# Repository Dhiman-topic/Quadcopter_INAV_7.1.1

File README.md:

# Quadcopter_INAV_7.1.1
 This project is about to make a home made quadcopter using aluminium frame and diy pcb

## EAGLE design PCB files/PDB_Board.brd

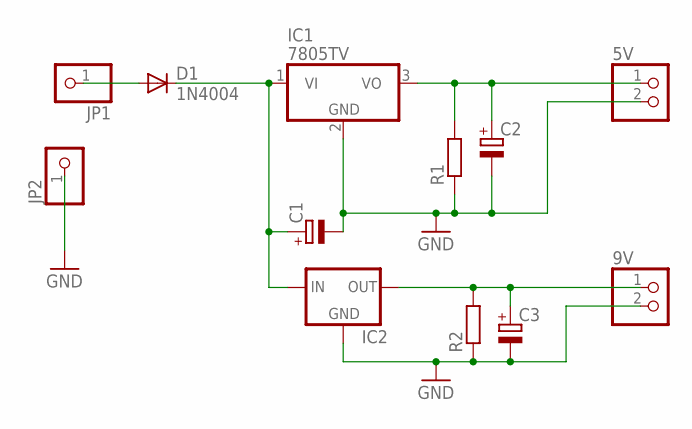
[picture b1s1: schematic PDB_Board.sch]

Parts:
5V, 9V: PINHD-1X2/OCT; 1X02/OCT
C1: CPOL-EUE3.5-8; E3,5-8
C2, C3: CPOL-EUE2.5-5; E2,5-5
D1: 1N4004; DO41-10
IC1: 7805TV; TO220V
IC2: 78XXS
JP1, JP2: PINHD-1X1; 1X01
R1, R2: R-EU_0207/10; 0207/10

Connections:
GND: 5V.2, 9V.2, C1.-, C2.-, C3.-, IC1.2 (GND), IC2.GND, JP2.1, R1.1, R2.1
unnamed: C1.+, D1.C, IC1.1 (VI), IC2.IN
unnamed: 9V.1, C3.+, IC2.OUT, R2.2
unnamed: 5V.1, C2.+, IC1.3 (VO), R1.2
unnamed: D1.A, JP1.1

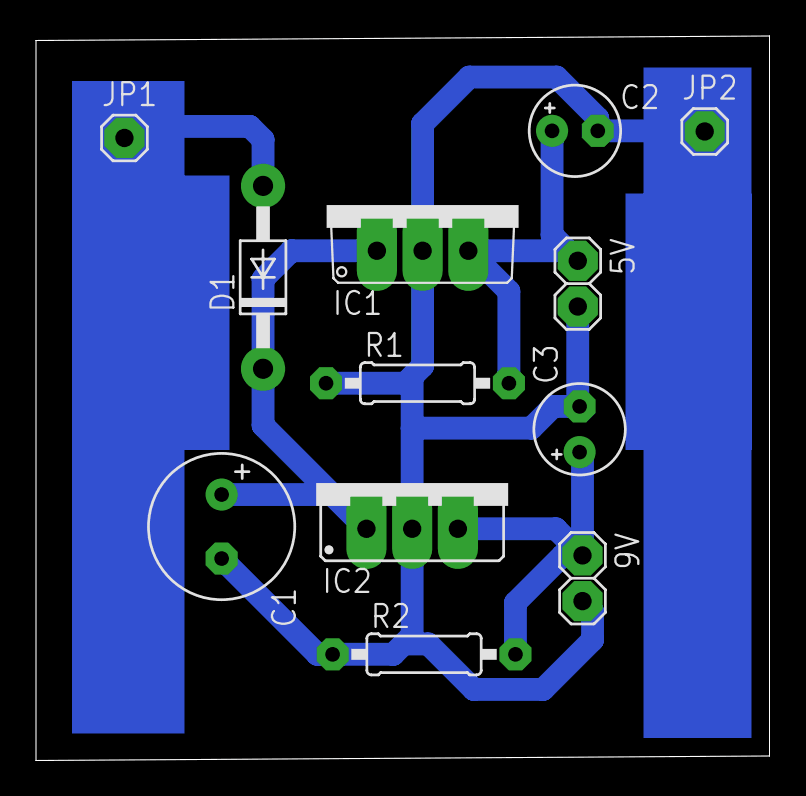
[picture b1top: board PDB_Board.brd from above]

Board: 2 copper layers, 40.8 x 40.2 mm, 12 parts (0 on the bottom side), 5 nets.

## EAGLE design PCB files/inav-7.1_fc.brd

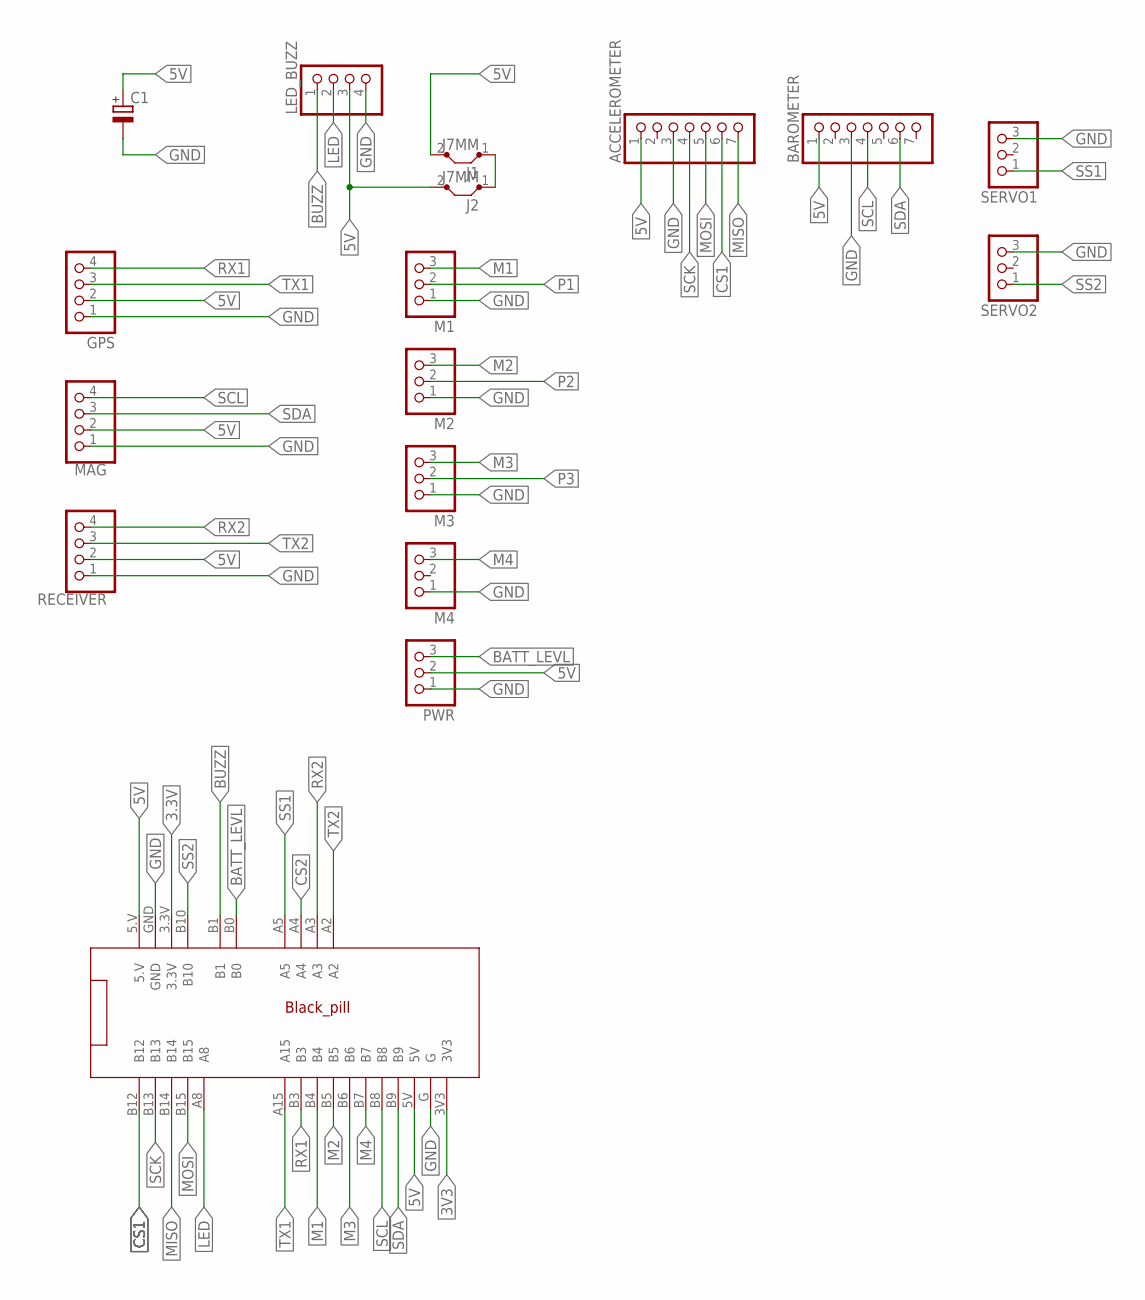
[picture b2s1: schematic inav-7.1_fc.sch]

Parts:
ACCELEROMETER: PINHD-1X7; 1X07
BAROMETER: PINHD-1X7; 1X07
C1: CPOL-EUE3.5-8; E3,5-8
GPS: PINHD-1X4; 1X04
J1, J2: J7MM; 07
LED_BUZZ: PINHD-1X4/OCT; 1X04/OCT
M1, M2, M3, M4: PINHD-1X3/OCT; 1X03/OCT
MAG: QWIIC_RIGHT_ANGLE; 1X04
PWR: PINHD-1X3/OCT; 1X03/OCT
RECEIVER: QWIIC_RIGHT_ANGLE; 1X04
SERVO1, SERVO2: PINHD-1X3/OCT; 1X03/OCT
U$1: BLACKPILL_FR_INAV7.1; BLACKPILLBOARD

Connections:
3.3V: U$1.3.3V
3V3: U$1.3V3
5V: ACCELEROMETER.1, BAROMETER.1, C1.+, GPS.2, J1.2, J2.2, LED_BUZZ.3, MAG.2, PWR.2, RECEIVER.2, U$1.5.V, U$1.5V
BATT_LEVL: PWR.3, U$1.B0
BUZZ: LED_BUZZ.1, U$1.B1
CS1: ACCELEROMETER.6, U$1.B12
CS2: U$1.A4
GND: ACCELEROMETER.3, BAROMETER.3, C1.-, GPS.1, LED_BUZZ.4, M1.1, M2.1, M3.1, M4.1, MAG.1, PWR.1, RECEIVER.1, SERVO1.3, SERVO2.3, U$1.G, U$1.GND
LED: LED_BUZZ.2, U$1.A8
M1: M1.3, U$1.B4
M2: M2.3, U$1.B5
M3: M3.3, U$1.B6
M4: M4.3, U$1.B7
MISO: ACCELEROMETER.7, U$1.B14
MOSI: ACCELEROMETER.5, U$1.B15
unnamed: J1.1, J2.1
P1: M1.2
P2: M2.2
P3: M3.2
RX1: GPS.4, U$1.B3
RX2: RECEIVER.4, U$1.A3
SCK: ACCELEROMETER.4, U$1.B13
SCL: BAROMETER.4, MAG.4, U$1.B8
SDA: BAROMETER.6, MAG.3, U$1.B9
SS1: SERVO1.1, U$1.A5
SS2: SERVO2.1, U$1.B10
TX1: GPS.3, U$1.A15
TX2: RECEIVER.3, U$1.A2

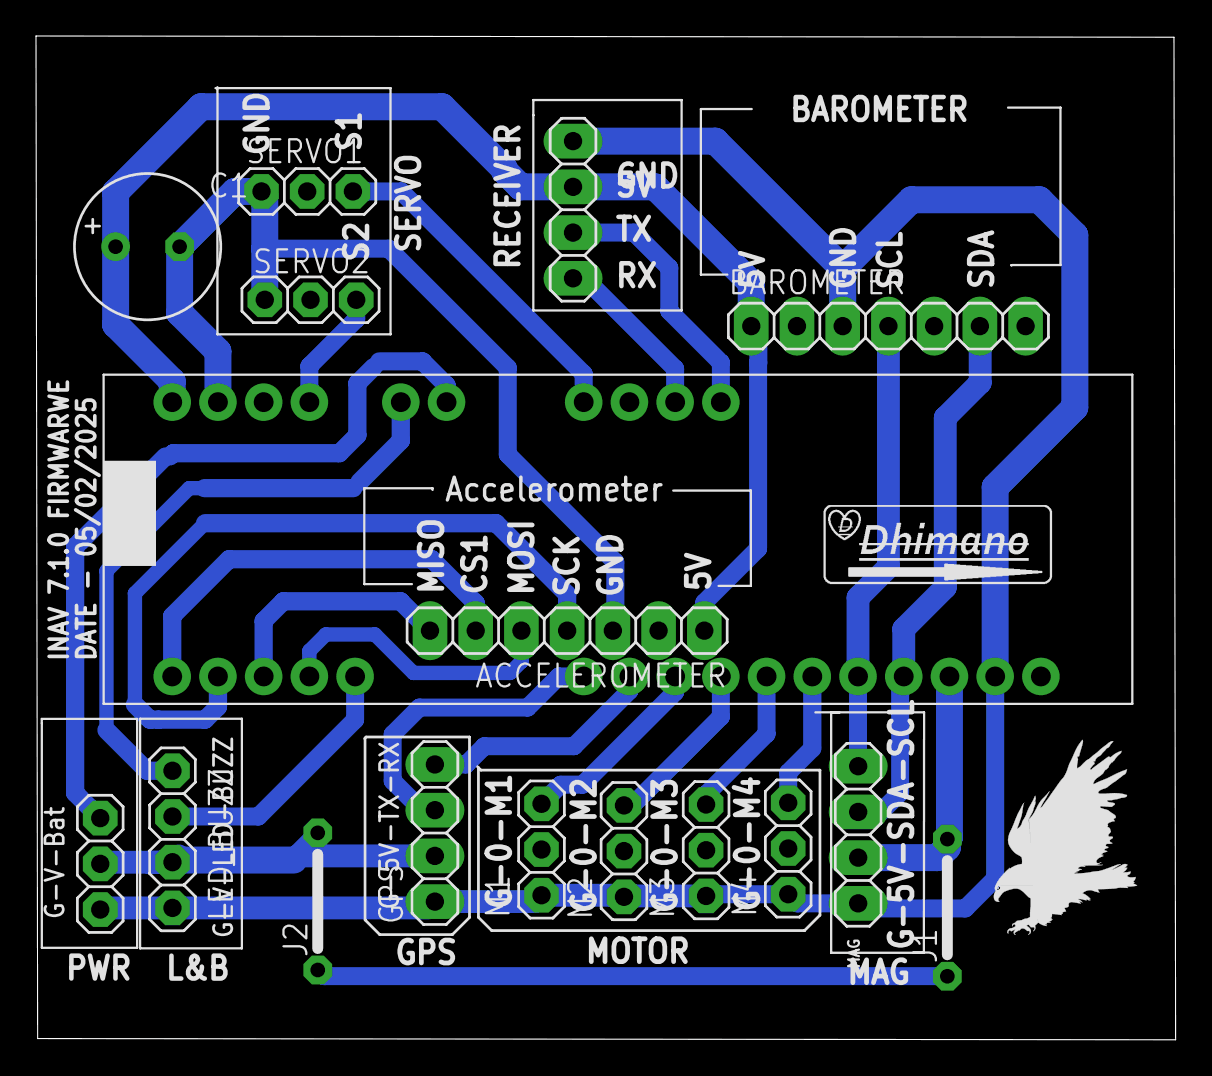
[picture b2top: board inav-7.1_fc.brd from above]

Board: 2 copper layers, 63.3 x 55.8 mm, 19 parts (0 on the bottom side), 22 nets.

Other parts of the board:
U$2: EAGLE-PLC-8MM
U$3: DHIMAN_LOGO_13_MIL

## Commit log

2025-04-22 change
